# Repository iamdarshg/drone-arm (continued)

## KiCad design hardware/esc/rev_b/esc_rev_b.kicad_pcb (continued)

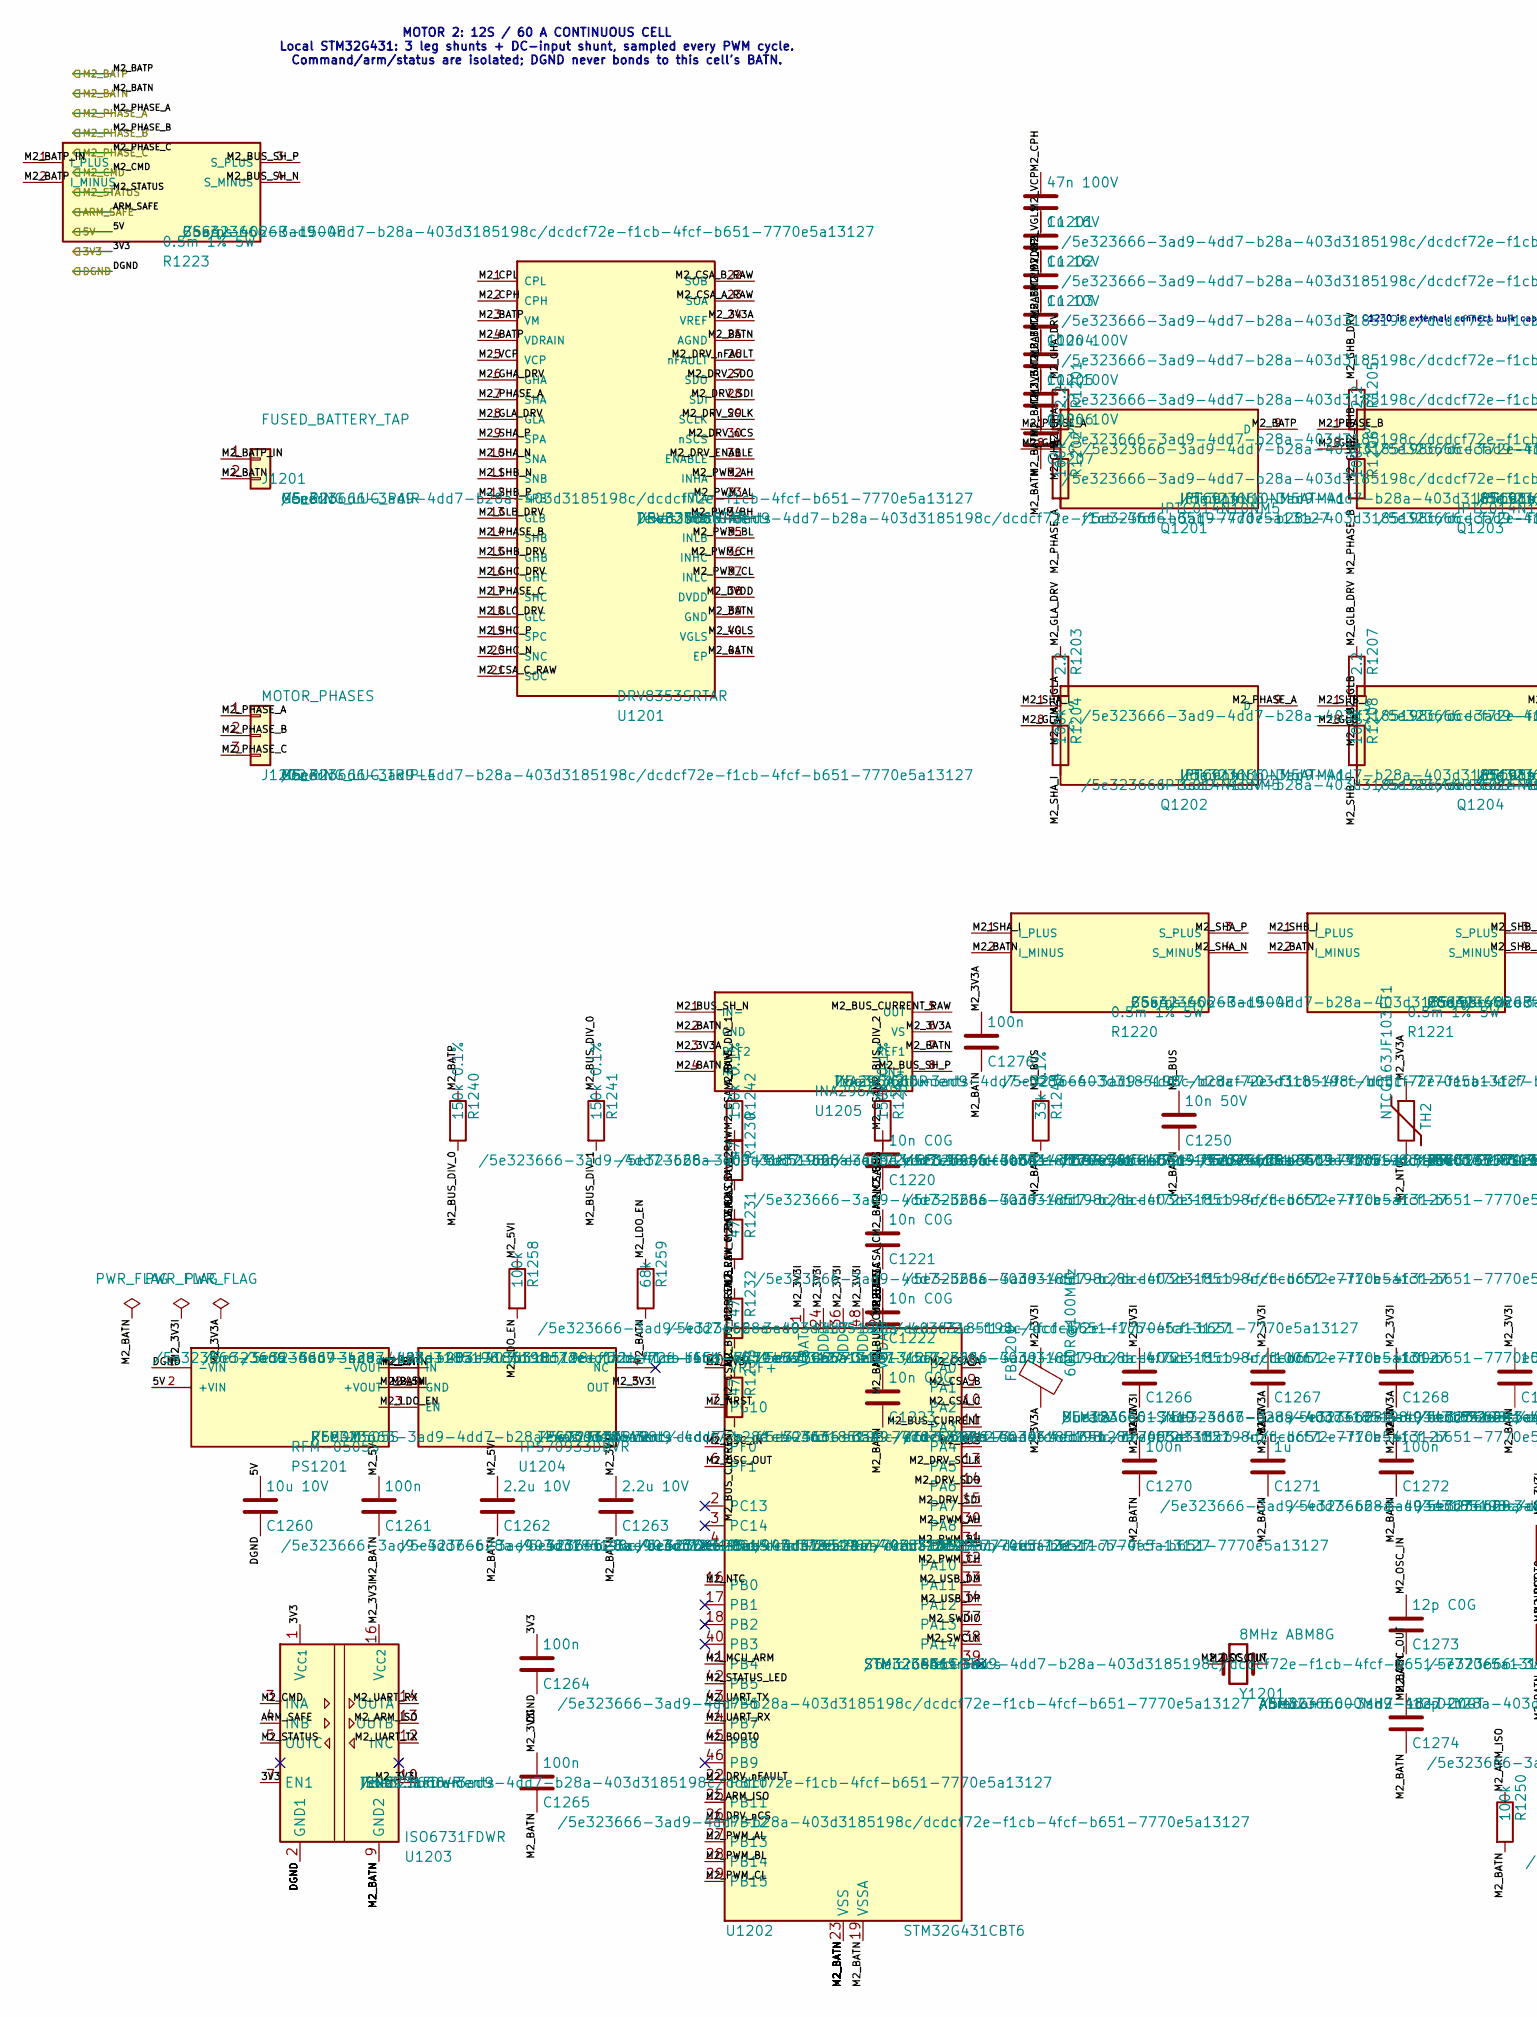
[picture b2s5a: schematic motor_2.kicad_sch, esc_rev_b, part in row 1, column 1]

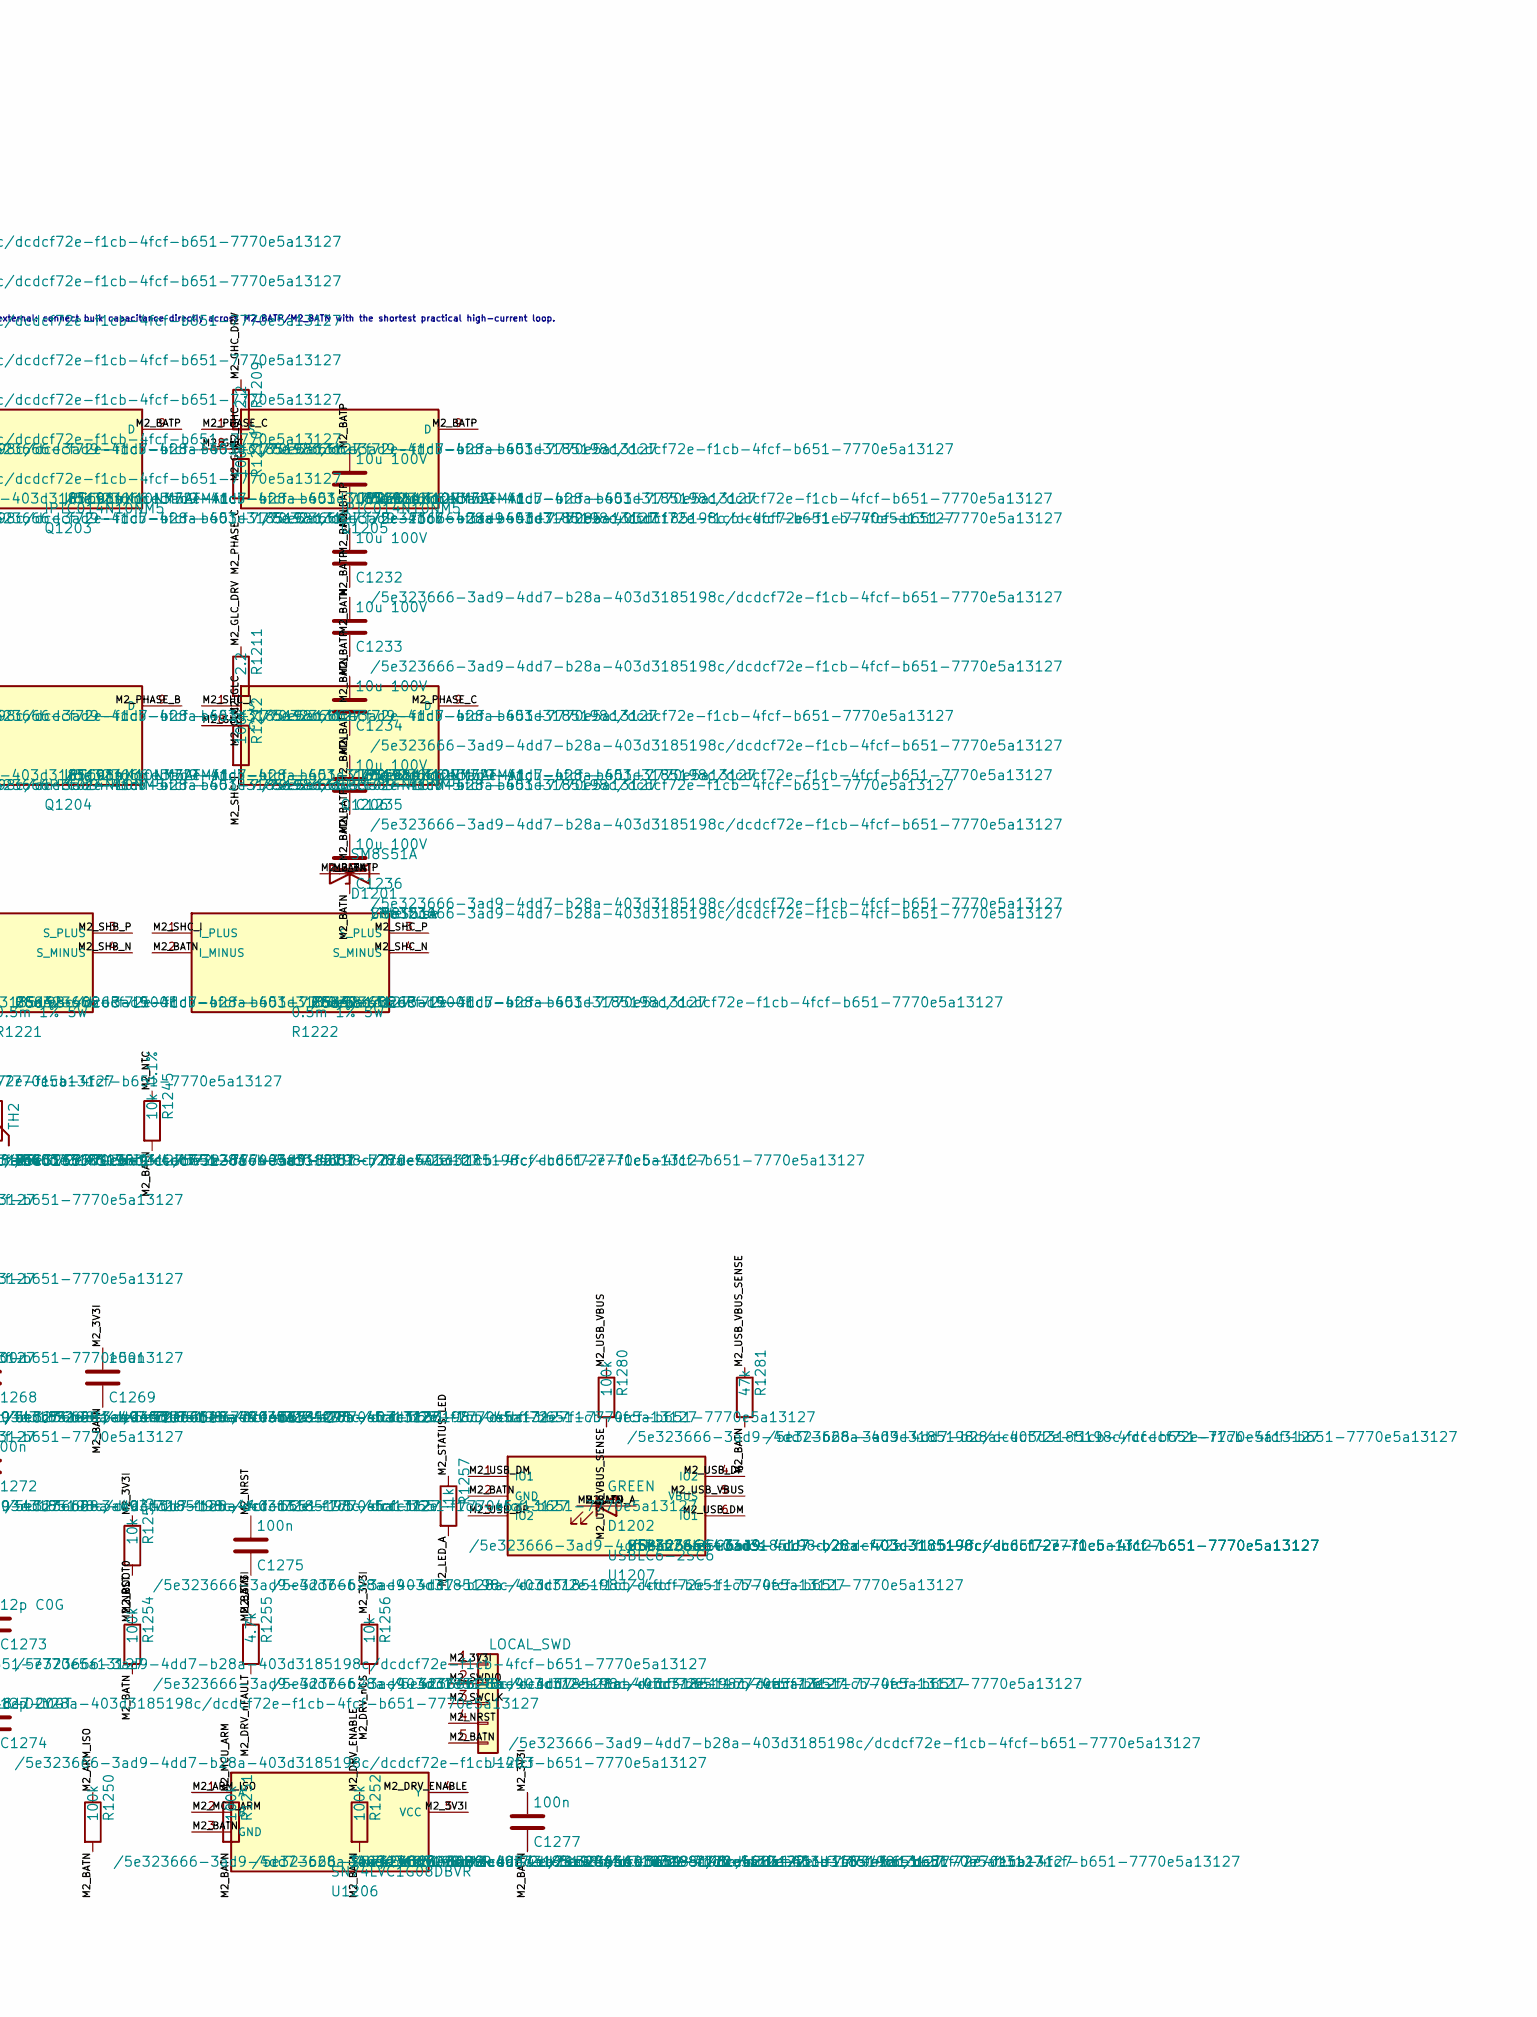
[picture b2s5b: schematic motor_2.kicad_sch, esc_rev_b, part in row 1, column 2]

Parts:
C1201: 47n 100V; C_0603_1608Metric
C1202, C1203: 1u 16V; C_0603_1608Metric
C1204: 1u 10V; C_0603_1608Metric
C1205: 100n 100V; C_0603_1608Metric
C1206, C1231, C1232, C1233, C1234, C1235, C1236: 10u 100V; C_1210_3225Metric
C1207: 100n 10V; C_0603_1608Metric
C1220, C1221, C1222, C1223: 10n C0G; C_0603_1608Metric
C1250: 10n 50V; C_0603_1608Metric
C1260: 10u 10V; C_0805_2012Metric
C1261, C1264, C1265, C1275, C1276, C1277: 100n; C_0603_1608Metric
C1262, C1263: 2.2u 10V; C_0603_1608Metric
C1266: 4.7u; C_0603_1608Metric
C1267, C1268, C1269, C1270, C1272: 100n; C_0402_1005Metric
C1271: 1u; C_0603_1608Metric
C1273, C1274: 12p C0G; C_0402_1005Metric
D1201: SM8S51A; DO-218AB_SM8S; MPN SM8S51A
D1202: GREEN; LED_0603_1608Metric
FB1201: 600R@100MHz; L_0603_1608Metric; MPN BLM18AG601SN1D
J1201: FUSED_BATTERY_TAP; POWER_LUG_M5_2P_P20; MPN M5_RING_LUG_PAIR
J1202: MOTOR_PHASES; POWER_LUG_M5_3P_P20; MPN M5_RING_LUG_TRIPLE
J1203: LOCAL_SWD; PinHeader_1x05_P1.27mm_Vertical
PS1201: RFM-0505S; RFM_SIP4_11.5x6_P2.54; MPN RFM-0505S
Q1201, Q1202, Q1203, Q1204, Q1205, Q1206: IPTC014N10NM5; PG-HDSOP-16_TOLT_IPTC; MPN IPTC014N10NM5ATMA1
R1201, R1203, R1205, R1207, R1209, R1211: 2.2; R_0603_1608Metric
R1202, R1204, R1206, R1208, R1210, R1212, R1250, R1251, R1252, R1254, R1258, R1280: 100k; R_0603_1608Metric
R1220, R1221, R1222, R1223: 0.5m 1% 5W; CSS4J-4026_Kelvin; MPN CSS4J-4026R-L500F
R1230, R1231, R1232, R1233: 47; R_0603_1608Metric
R1240, R1241, R1242, R1243: 150k 0.1%; R_1206_3216Metric
R1244: 33k 0.1%; R_0603_1608Metric
R1245: 10k 0.1%; R_0603_1608Metric
R1253, R1256: 10k; R_0603_1608Metric
R1255: 4.7k; R_0603_1608Metric
R1257: 1k; R_0603_1608Metric
R1259: 68k; R_0603_1608Metric
R1281: 47k; R_0603_1608Metric
TH2: NTCG163JF103FT1; R_0603_1608Metric; MPN NTCG163JF103FT1
U1201: DRV8353SRTAR; WQFN-40-EP_6x6_P0.5; MPN DRV8353SRTAR
U1202: STM32G431CBT6; LQFP-48_7x7mm_P0.5mm; MPN STM32G431CBT6
U1203: ISO6731FDWR; SOIC-16W_7.5x10.3mm_P1.27mm; MPN ISO6731FDWR
U1204: TPS70933DBVR; SOT-23-5; MPN TPS70933DBVR
U1205: INA296A2IDR; SOIC-8_3.9x4.9mm_P1.27mm; MPN INA296A2IDR
U1206: SN74LVC1G08DBVR; SOT-23-5; MPN SN74LVC1G08DBVR
U1207: USBLC6-2SC6; SOT-23-6; MPN USBLC6-2SC6
Y1201: 8MHz ABM8G; Crystal_SMD_3225-4Pin_3.2x2.5mm; MPN ABM8G-8.000MHZ-18-D2Y-T

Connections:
/3V3: C1264.1, U1203.1 (V_{CC1}), U1203.7 (EN1); also elsewhere on the board
/5V: C1260.1, PS1201.2 (+VIN); also elsewhere on the board
/ARM_SAFE: U1203.4 (INB); also elsewhere on the board
/DGND: C1260.2, C1264.2, PS1201.1 (-VIN), U1203.2 (GND1), U1203.8 (GND1); also elsewhere on the board
/M2_BATN: C1203.2, C1204.2, C1205.2, C1206.2, C1207.2, C1220.2, C1221.2, C1222.2, C1223.2, C1231.2, C1232.2, C1233.2, C1234.2, C1235.2, C1236.2, C1250.2, C1261.2, C1262.2, C1263.2, C1265.2, C1266.2, C1267.2, C1268.2, C1269.2, C1270.2, C1271.2, C1272.2, C1273.2, C1274.2, C1275.2, C1276.2, C1277.2, D1201.1 (A1), D1202.1 (K), J1201.2, J1203.5, PS1201.3 (-VOUT), R1220.2 (I_MINUS), R1221.2 (I_MINUS), R1222.2 (I_MINUS), R1244.2, R1245.2, R1250.2, R1251.2, R1252.2, R1254.2, R1259.2, R1281.2, U1201.25 (AGND), U1201.39 (GND), U1201.41 (EP), U1202.19 (VSSA), U1202.23 (VSS), U1202.35 (VSS), U1202.47 (VSS), U1203.9 (GND2), U1203.15 (GND2), U1204.2 (GND), U1205.2 (GND), U1205.4 (NC), U1205.7 (REF1), U1206.3 (GND), U1207.2 (GND); also elsewhere on the board
/M2_BATP: C1202.2, C1205.1, C1206.1, C1231.1, C1232.1, C1233.1, C1234.1, C1235.1, C1236.1, D1201.2 (A2), Q1201.9 (D), Q1203.9 (D), Q1205.9 (D), R1223.2 (I_MINUS), R1240.1, U1201.3 (VM), U1201.4 (VDRAIN); also elsewhere on the board
/M2_CMD: U1203.3 (INA); also elsewhere on the board
/M2_PHASE_A: J1202.1, Q1201.1 (S), Q1202.9 (D), R1202.2, U1201.7 (SHA)
/M2_PHASE_B: J1202.2, Q1203.1 (S), Q1204.9 (D), R1206.2, U1201.14 (SHB)
/M2_PHASE_C: J1202.3, Q1205.1 (S), Q1206.9 (D), R1210.2, U1201.17 (SHC)
/M2_STATUS: U1203.5 (OUTC); also elsewhere on the board
/Motor 2 power cell/M2_3V3A: C1207.1, C1271.1, C1272.1, C1276.1, FB1201.2, TH2.1, U1201.24 (VREF), U1202.20 (VREF+), U1202.21 (VDDA), U1205.3 (REF2), U1205.6 (VS)
/Motor 2 power cell/M2_3V3I: C1263.1, C1265.1, C1266.1, C1267.1, C1268.1, C1269.1, C1270.1, C1277.1, FB1201.1, J1203.1, R1253.1, R1255.1, R1256.1, U1202.1 (VBAT), U1202.24 (VDD), U1202.36 (VDD), U1202.48 (VDD), U1203.10 (EN2), U1203.16 (V_{CC2}), U1204.5 (OUT), U1206.5 (VCC)
/Motor 2 power cell/M2_5VI: C1261.1, C1262.1, PS1201.4 (+VOUT), R1258.1, U1204.1 (IN)
/Motor 2 power cell/M2_ARM_ISO: R1250.1, U1202.25 (PB11), U1203.13 (OUTB), U1206.1 (A)
/Motor 2 power cell/M2_BATP_IN: J1201.1, R1223.1 (I_PLUS)
/Motor 2 power cell/M2_BOOT0: R1254.1, U1202.45 (PB8)
/Motor 2 power cell/M2_BUS: C1250.1, R1243.2, R1244.1, U1202.12 (PA4)
/Motor 2 power cell/M2_BUS_CURRENT: C1223.1, R1233.2, U1202.11 (PA3)
/Motor 2 power cell/M2_BUS_CURRENT_RAW: R1233.1, U1205.5 (OUT)
/Motor 2 power cell/M2_BUS_DIV_0: R1240.2, R1241.1
/Motor 2 power cell/M2_BUS_DIV_1: R1241.2, R1242.1
/Motor 2 power cell/M2_BUS_DIV_2: R1242.2, R1243.1
/Motor 2 power cell/M2_BUS_SH_N: R1223.4 (S_MINUS), U1205.1 (IN-)
/Motor 2 power cell/M2_BUS_SH_P: R1223.3 (S_PLUS), U1205.8 (IN+)
/Motor 2 power cell/M2_CPH: C1201.1, U1201.2 (CPH)
/Motor 2 power cell/M2_CPL: C1201.2, U1201.1 (CPL)
/Motor 2 power cell/M2_CSA_A: C1220.1, R1230.2, U1202.8 (PA0)
/Motor 2 power cell/M2_CSA_A_RAW: R1230.1, U1201.23 (SOA)
/Motor 2 power cell/M2_CSA_B: C1221.1, R1231.2, U1202.9 (PA1)
/Motor 2 power cell/M2_CSA_B_RAW: R1231.1, U1201.22 (SOB)
/Motor 2 power cell/M2_CSA_C: C1222.1, R1232.2, U1202.10 (PA2)
/Motor 2 power cell/M2_CSA_C_RAW: R1232.1, U1201.21 (SOC)
/Motor 2 power cell/M2_DRV_ENABLE: R1252.1, U1201.31 (ENABLE), U1206.4 (Y)
/Motor 2 power cell/M2_DRV_SCLK: U1201.29 (SCLK), U1202.13 (PA5)
/Motor 2 power cell/M2_DRV_SDI: U1201.28 (SDI), U1202.15 (PA7)
/Motor 2 power cell/M2_DRV_SDO: U1201.27 (SDO), U1202.14 (PA6)
/Motor 2 power cell/M2_DRV_nCS: R1256.2, U1201.30 (nSCS), U1202.26 (PB12)
/Motor 2 power cell/M2_DRV_nFAULT: R1255.2, U1201.26 (nFAULT), U1202.22 (PB10)
/Motor 2 power cell/M2_DVDD: C1204.1, U1201.38 (DVDD)
/Motor 2 power cell/M2_GHA: Q1201.8 (G), R1201.2, R1202.1
/Motor 2 power cell/M2_GHA_DRV: R1201.1, U1201.6 (GHA)
/Motor 2 power cell/M2_GHB: Q1203.8 (G), R1205.2, R1206.1
/Motor 2 power cell/M2_GHB_DRV: R1205.1, U1201.15 (GHB)
/Motor 2 power cell/M2_GHC: Q1205.8 (G), R1209.2, R1210.1
/Motor 2 power cell/M2_GHC_DRV: R1209.1, U1201.16 (GHC)
/Motor 2 power cell/M2_GLA: Q1202.8 (G), R1203.2, R1204.1
/Motor 2 power cell/M2_GLA_DRV: R1203.1, U1201.8 (GLA)
/Motor 2 power cell/M2_GLB: Q1204.8 (G), R1207.2, R1208.1
/Motor 2 power cell/M2_GLB_DRV: R1207.1, U1201.13 (GLB)
/Motor 2 power cell/M2_GLC: Q1206.8 (G), R1211.2, R1212.1
/Motor 2 power cell/M2_GLC_DRV: R1211.1, U1201.18 (GLC)
/Motor 2 power cell/M2_LDO_EN: R1258.2, R1259.1, U1204.3 (EN)
/Motor 2 power cell/M2_LED_A: D1202.2 (A), R1257.2
/Motor 2 power cell/M2_MCU_ARM: R1251.1, U1202.41 (PB4), U1206.2 (B)
/Motor 2 power cell/M2_NRST: C1275.1, J1203.4, R1253.2, U1202.7 (PG10)
/Motor 2 power cell/M2_NTC: R1245.1, TH2.2, U1202.16 (PB0)
/Motor 2 power cell/M2_OSC_IN: C1273.1, U1202.5 (PF0), Y1201.1
/Motor 2 power cell/M2_OSC_OUT: C1274.1, U1202.6 (PF1), Y1201.2
/Motor 2 power cell/M2_PWM_AH: U1201.32 (INHA), U1202.30 (PA8)
/Motor 2 power cell/M2_PWM_AL: U1201.33 (INLA), U1202.27 (PB13)
/Motor 2 power cell/M2_PWM_BH: U1201.34 (INHB), U1202.31 (PA9)
/Motor 2 power cell/M2_PWM_BL: U1201.35 (INLB), U1202.28 (PB14)
/Motor 2 power cell/M2_PWM_CH: U1201.36 (INHC), U1202.32 (PA10)
/Motor 2 power cell/M2_PWM_CL: U1201.37 (INLC), U1202.29 (PB15)
/Motor 2 power cell/M2_SHA_I: Q1202.1 (S), R1204.2, R1220.1 (I_PLUS)
/Motor 2 power cell/M2_SHA_N: R1220.4 (S_MINUS), U1201.10 (SNA)
/Motor 2 power cell/M2_SHA_P: R1220.3 (S_PLUS), U1201.9 (SPA)
/Motor 2 power cell/M2_SHB_I: Q1204.1 (S), R1208.2, R1221.1 (I_PLUS)
/Motor 2 power cell/M2_SHB_N: R1221.4 (S_MINUS), U1201.11 (SNB)
/Motor 2 power cell/M2_SHB_P: R1221.3 (S_PLUS), U1201.12 (SPB)
/Motor 2 power cell/M2_SHC_I: Q1206.1 (S), R1212.2, R1222.1 (I_PLUS)
/Motor 2 power cell/M2_SHC_N: R1222.4 (S_MINUS), U1201.20 (SNC)
/Motor 2 power cell/M2_SHC_P: R1222.3 (S_PLUS), U1201.19 (SPC)
/Motor 2 power cell/M2_STATUS_LED: R1257.1, U1202.42 (PB5)
/Motor 2 power cell/M2_SWCLK: J1203.3, U1202.38 (PA14)
/Motor 2 power cell/M2_SWDIO: J1203.2, U1202.37 (PA13)
/Motor 2 power cell/M2_UART_RX: U1202.44 (PB7), U1203.14 (OUTA)
/Motor 2 power cell/M2_UART_TX: U1202.43 (PB6), U1203.12 (INC)
/Motor 2 power cell/M2_USB_DM: U1202.33 (PA11), U1207.1 (IO1), U1207.6 (IO1)
/Motor 2 power cell/M2_USB_DP: U1202.34 (PA12), U1207.3 (IO2), U1207.4 (IO2)
/Motor 2 power cell/M2_USB_VBUS: R1280.1, U1207.5 (VBUS)
/Motor 2 power cell/M2_USB_VBUS_SENSE: R1280.2, R1281.1
/Motor 2 power cell/M2_VCP: C1202.1, U1201.5 (VCP)
/Motor 2 power cell/M2_VGLS: C1203.1, U1201.40 (VGLS)

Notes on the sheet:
MOTOR 2: 12S / 60 A CONTINUOUS CELL Local STM32G431: 3 leg shunts + DC-input shunt, sampled every PWM cycle. Command/arm/status are isolated; DGND never bonds to this cell's BATN.
C1230 is external: connect bulk capacitance directly across M2_BATP/M2_BATN with the shortest practical high-current loop.
